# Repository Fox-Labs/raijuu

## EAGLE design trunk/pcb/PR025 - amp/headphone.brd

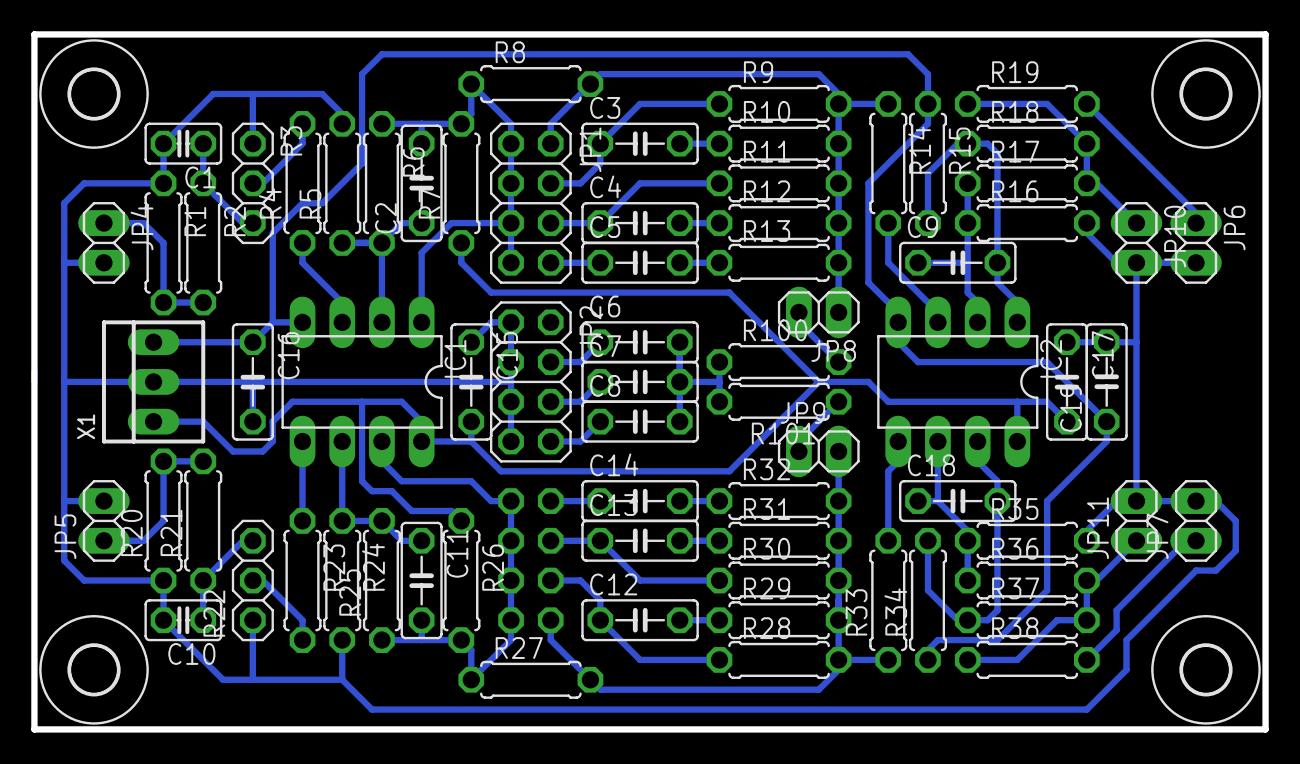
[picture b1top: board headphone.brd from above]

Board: 2 copper layers, 78.7 x 44.5 mm, 77 parts (1 on the bottom side), 45 nets.

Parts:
C1, C10: 220pF; C025-025X050
C2, C9, C11, C18: 10pF; C050-025X075
C3, C12: 200nF; C050-025X075
C4, C13: 140nF; C050-025X075
C5, C14, C15, C16, C17, C19: 100nF; C050-025X075
C6: 47nF; C050-025X075
C7: 30nF; C050-025X075
C8: 22nF; C050-025X075
IC1, IC2: OPA2134PA; DIL08
JP1, JP2, JP3: 2X04
JP4, JP5, JP6, JP7, JP8, JP9, JP10, JP11: 1X02
R1, R20: 47k; 0207/7
R2, R21, R100, R101: 2.2k; 0207/7
R3, R22: 10k; 1X03
R4, R23: 1k; 0207/7
R5, R14, R17, R24, R33, R36: 4.7k; 0207/7
R6, R16, R25, R35: 10k; 0207/7
R7, R15, R26, R34: 1.5k; 0207/7
R8, R27: 4.4k; 0207/7
R9, R28: 3.6k; 0207/7
R10, R12, R13, R29, R31, R32: 330; 0207/7
R11, R30: 9.5k; 0207/7
R18, R37: 47; 0207/7
R19, R38: 120; 0207/7
U$1, U$2, U$3, U$4: 3,0
X1: 22-23-2031

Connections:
+12V: C15.2, C17.2, IC1.8, IC2.8, R7.1, R26.1, X1.1
-12V: C16.1, C19.1, IC1.4, IC2.4, R15.1, R34.1, X1.3
AGND: C1.2, C10.2, C15.1, C16.2, C17.1, C19.2, JP2.1, JP2.3, JP2.5, JP2.7, JP4.2, JP5.2, JP6.2, JP7.2, JP10.2, JP11.2, R1.1, R3.1, R5.2, R16.2, R20.1, R22.1, R24.2, R35.2, X1.2
IN_L: JP4.1, R1.2, R2.2
IN_R: JP5.1, R20.2, R21.2
unnamed: JP9.1, R101.1
unnamed: C1.1, R2.1, R3.3
unnamed: R3.2, R4.2
unnamed: JP1.2, JP8.1, R8.2, R9.2, R10.2, R11.2, R12.2, R13.2, R14.1
unnamed: IC1.3, R4.1
unnamed: C2.1, IC1.2, R5.1, R6.2
unnamed: C2.2, IC1.1, JP1.1, JP1.3, JP1.5, JP1.7, R6.1, R7.2, R8.1
unnamed: C3.2, R10.1
unnamed: C3.1, JP1.4, R9.1
unnamed: C5.2, R13.1
unnamed: C4.2, R12.1
unnamed: C4.1, JP1.6, R11.1
unnamed: C5.1, JP1.8
unnamed: C6.1, JP2.4
unnamed: C7.1, JP2.6
unnamed: C8.1, JP2.8
unnamed: C6.2, C7.2, C8.2, R100.1, R101.2
unnamed: IC2.3, R14.2
unnamed: C9.1, IC2.2, R16.1, R17.1
unnamed: C9.2, IC2.1, R15.2, R18.1
unnamed: JP10.1, R17.2, R18.2, R19.1
unnamed: JP8.2, R100.2
unnamed: C10.1, R21.1, R22.3
unnamed: R22.2, R23.2
unnamed: IC1.5, R23.1
unnamed: C11.1, IC1.6, R24.1, R25.2
unnamed: C11.2, IC1.7, JP3.2, JP3.4, JP3.6, JP3.8, R25.1, R26.2, R27.1
unnamed: C12.2, R29.1
unnamed: C12.1, JP3.5, R28.1
unnamed: C13.2, R31.1
unnamed: C13.1, JP3.3, R30.1
unnamed: JP3.7, JP9.2, R27.2, R28.2, R29.2, R30.2, R31.2, R32.2, R33.1
unnamed: C14.2, R32.1
unnamed: C14.1, JP3.1
unnamed: IC2.5, R33.2
unnamed: C18.1, IC2.6, R35.1, R36.1
unnamed: C18.2, IC2.7, R34.2, R37.1
unnamed: JP11.1, R36.2, R37.2, R38.1
OUT_L: JP6.1, R19.2
OUT_R: JP7.1, R38.2

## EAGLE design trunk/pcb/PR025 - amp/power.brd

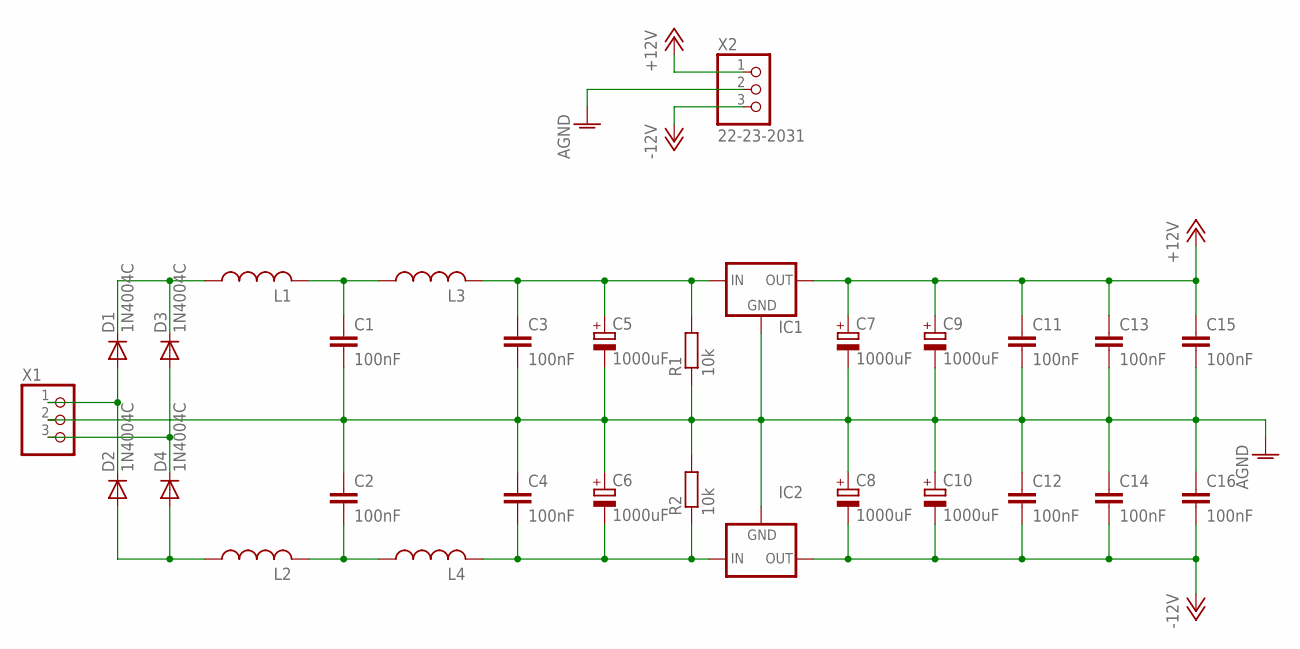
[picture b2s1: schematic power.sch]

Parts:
C1, C2, C3, C4, C11, C12, C13, C14, C15, C16: 100nF; C050-045X075
C5, C6, C7, C8, C9, C10: 1000uF; E5-13
D1, D2, D3, D4: 1N4004C; DO41-10
IC1: 78XXTO-220; 78XXS
IC2: 79XXTO-220; 79XXS
L1, L2, L3, L4: L-US075-063X106; L075-063X106
R1, R2: 10k; 0207/2V
X1: W237-103
X2: 22-23-2031

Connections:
+12V: C7.+, C9.+, C11.1, C13.1, C15.1, IC1.OUT, X2.1
-12V: C8.-, C10.-, C12.2, C14.2, C16.2, IC2.OUT, X2.3
AGND: C1.2, C2.1, C3.2, C4.1, C5.-, C6.+, C7.-, C8.+, C9.-, C10.+, C11.2, C12.1, C13.2, C14.1, C15.2, C16.1, IC1.GND, IC2.GND, R1.1, R2.2, X1.2, X2.2
unnamed: C1.1, L1.2, L3.1
unnamed: C2.2, L2.2, L4.1
unnamed: C3.1, C5.+, IC1.IN, L3.2, R1.2
unnamed: C4.2, C6.-, IC2.IN, L4.2, R2.1
unnamed: D2.A, D4.A, L2.1
unnamed: D1.C, D3.C, L1.1
unnamed: D1.A, D2.C, X1.1
unnamed: D3.A, D4.C, X1.3

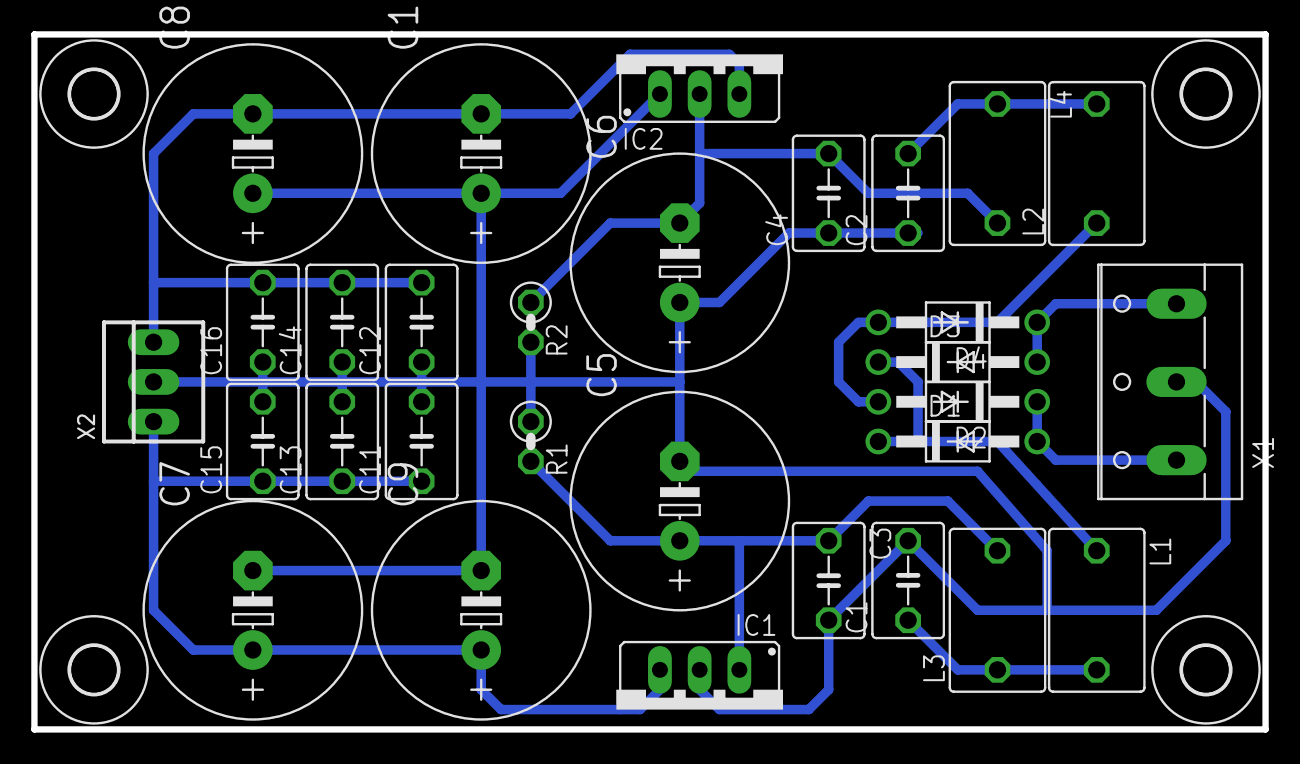
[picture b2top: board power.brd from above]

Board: 2 copper layers, 78.7 x 44.5 mm, 34 parts (0 on the bottom side), 11 nets.

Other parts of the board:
U$1, U$2, U$3, U$4: 3,0

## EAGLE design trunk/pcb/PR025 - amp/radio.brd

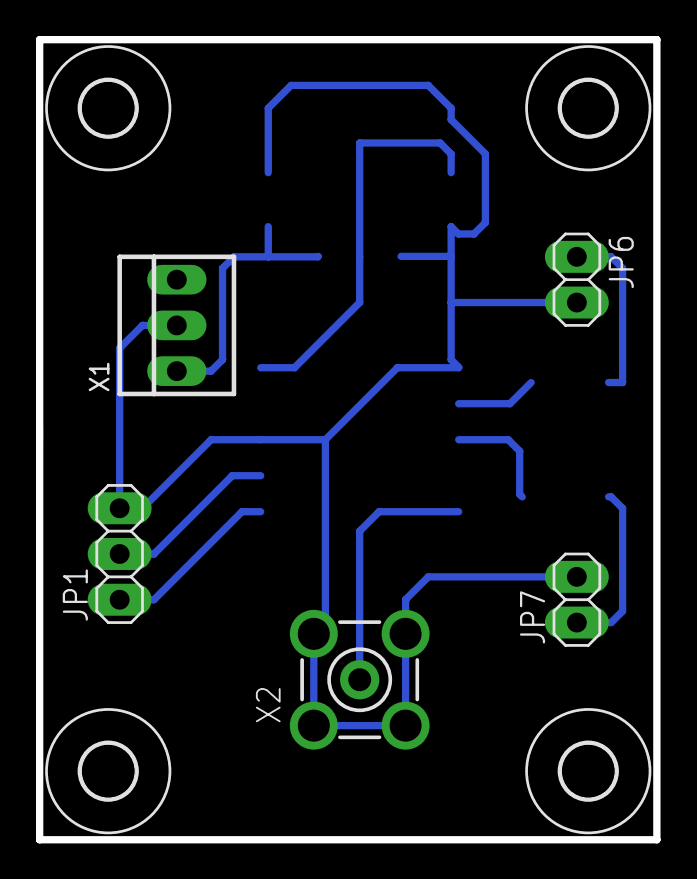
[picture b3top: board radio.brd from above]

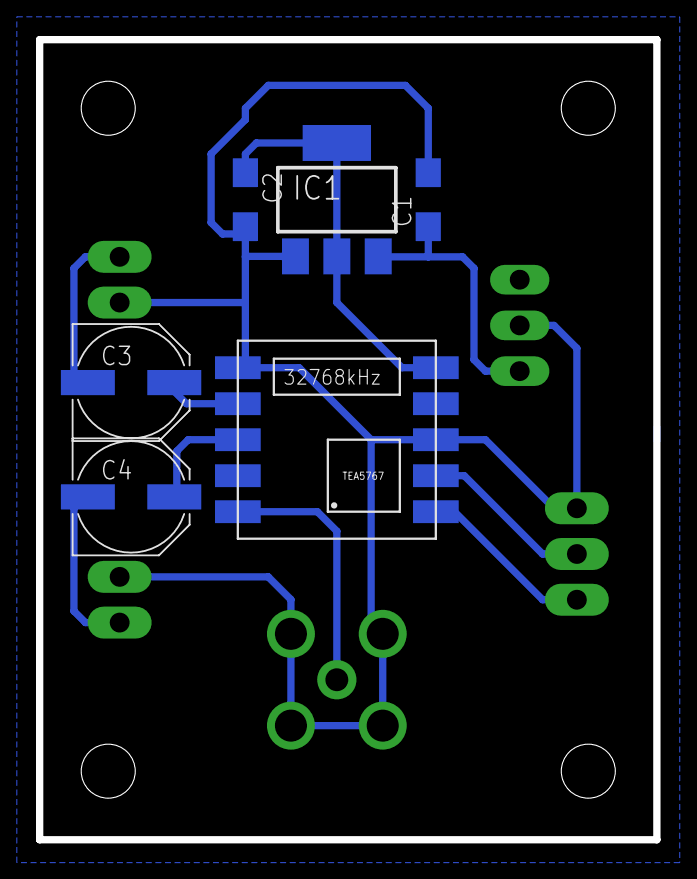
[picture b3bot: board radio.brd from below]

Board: 2 copper layers, 34.3 x 44.5 mm, 15 parts (6 on the bottom side), 10 nets.

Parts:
C1, C2: 1uF; SMC_A
C3, C4: 22uF; PANASONIC_D
IC1: LM1117S; SOT223
JP1: 1X03
JP6, JP7: 1X02
U1: TEA5767
U$1, U$2, U$3, U$4: 3,0
X1: 22-23-2031
X2: BU-SMA-V

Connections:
+3V3: C2.+, IC1.2, IC1.4, U1.5
+12V: C1.+, IC1.3, X1.1
GND: C1.-, C2.-, IC1.1, JP1.3, JP6.2, JP7.2, U1.3, U1.6, X1.2, X2.2, X2.3, X2.4, X2.5
unnamed: U1.10, X2.1
unnamed: C3.+, U1.7
unnamed: C3.-, JP6.1
unnamed: C4.-, JP7.1
OUT_R: C4.+, U1.8
SCL: JP1.2, U1.2
SDA: JP1.1, U1.1

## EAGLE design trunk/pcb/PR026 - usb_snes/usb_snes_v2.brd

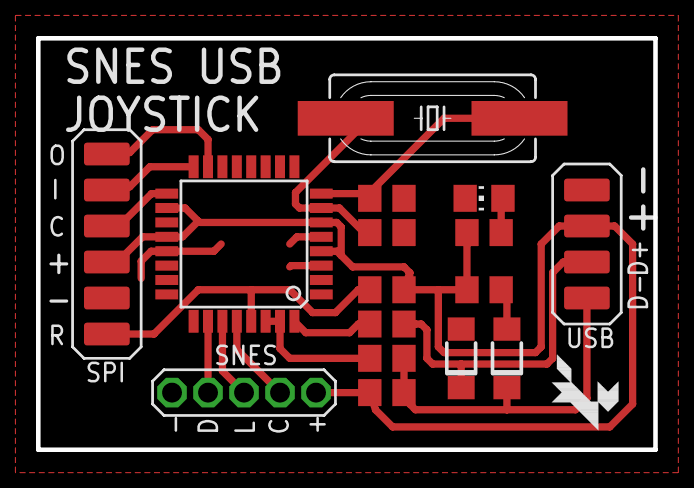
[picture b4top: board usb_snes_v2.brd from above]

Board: 2 copper layers, 34.3 x 22.9 mm, 17 parts (0 on the bottom side), 16 nets.

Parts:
C1, C2: 22pF; R0805
C3: 10uF; R0805
D1, D2: 3.6V; SOD123FL
IC1: AVR-MEGA8; TQFP32-08
IC2: SNES
JP1: 1X04-2MM
JP7: 1X06-2MM
LED1: CHIP-LED0805
Q1: HC49UP
R1: 10k; R0805
R2, R3: 68; R0805
R4: 1.5k; R0805
R5: 1k; R0805
U$1: FOX-1

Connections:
+5V: C3.1, IC1.4, IC1.6, IC1.18, IC1.20, IC2.5, JP1.2, JP7.4, R1.2, R4.1, R5.2
CLOCK: IC1.28, IC2.4
D+: D2.C, JP1.3, R3.1
D-: D1.C, JP1.4, R2.1, R4.2
DATA: IC1.26, IC2.2
GND: C1.1, C2.1, C3.2, D1.A, D2.A, IC1.3, IC1.5, IC1.21, IC2.1, JP1.1, JP7.5, LED1.C
LATCH: IC1.27, IC2.3
MISO: IC1.16, JP7.2
MOSI: IC1.15, JP7.1
unnamed: C2.2, IC1.8, Q1.1
unnamed: C1.2, IC1.7, Q1.2
unnamed: IC1.30, IC1.31, R2.2
unnamed: IC1.32, R3.2
unnamed: LED1.A, R5.1
RST: IC1.29, JP7.6, R1.1
SCK: IC1.17, JP7.3
